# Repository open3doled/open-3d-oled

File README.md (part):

# Open3DOLED 

## Beta Testers Needed
I'm looking for beta testers who have potentially compatible displays.
I have 49 partially assembled units.
If you have a 120hz TV and it is either and OLED with BFI (@120hz), or an LCD with fast pixel response time your display may work, checkout [this fantastic table](https://www.rtings.com/tv/tools/table/138933) provided by rtings.com for relevant display parameters.
Just to be clear the beta units are not free, but produced near cost and bundled with a pair of panasonic glasses with custom firmware optimized for software pageflipping (see below for details about this).
The price for the emitter and 1 pair of M size glasses is $100 USD with tracked global shipping.
I will help you configure the unit to work with your display and help with any trouble shooting, if the unit does not work with your TV you can return it for a refund (minus cost of shipping).
In return all I ask is that you share the config settings that work best with your TV.
If interested contact me at: support at open3doled dot com.

## Introduction
Open3DOLED is a set of software and hardware designs that allow one to turn any display into a 3D display using compatible shutter glasses.  
It works best for displays that incorporate Black Frame Insertion (BFI) technologies and have framerates that exceed 120hz.  
This includes OLED TV's by the likes of LG and Sony which incorporate technologies like LG "Motion Pro" and Sony "Clearness" settings.  
It can also work on LCD TV's and monitors that have fast pixel response time, in such cases it works best if the TV supports HDMI/DVI QFT (Quick Frame Transport), this can be used to force a large vertical blanking interval during which time the image on the LCD will be static.  
It also has been tested to work on the latest Sony micro-LED TV's.  
If your compatibility information for your TV is not listed below, or you are considering buying a TV and would like to know if it might be compatible I would suggest referring to [this fantastic table](https://www.rtings.com/tv/tools/table/138933) provided by rtings.com  
You can compare, sort and filter by pixel response time, support for BFI 120hz, BFI duty cycle, PWM backlight fruency and duty cycle.  
In addition to the RTINGs website you will also need to confirm the orientation of the front polarizer on your TV. 
Most TV's have a vertical front polarizer, but about 10% have a horizontal front polarizer. 
In the event you have have one of these TV's there is a $30 USD extra fee for me to flip the front polarizer on each pair of glasses.
I have measured the front polarization of over 70 different modern TV's and provided them in the FAQ, if your TV isn't listed you can check the front polarization using a pair of polarized sunglasses from the dollar store. 
Polarized sunglasses are vertically polarizer, just like the majority of TVs so if you can see the TV throught the glasses then your TV has a vertical front polarizer (or no polarizer at all).
There is a webstore in the works where you will be able to buy a pre-built/pre-programmed emitter unit in the next month or so once preliminary beta testing is complete..  
In the future custom firmware images that are optimized for software pageflipping for popular brands of glasses by Panasonic (and other manufacturers) may be released.  
(I plan to sell these glasses on the webstore initially along with the emitters to help recoup the over 400(?) hours put into this project, they reduce jitter greatly and eliminate crosstalk from dropped frames)  
Gaming is also supported through the use [Geo3D](https://github.com/open3doled/Geo3D/releases) and [WibbleWobble](https://github.com/PHARTGAMES/WibbleWobbleCore) see below for more details.

## Glasses Warning
* If you are using Panasonic Gen2 (TY-EW3D2XX) glasses, do NOT turn them on while a USB charging cable is attached or you risk destroying the left shutter element from DC bias.
* If you are using Panasonic Gen3 (TY-EW3D3XX) glasses, ONLY use a micro-usb power cable (like the one included), do not use a micro-usb cable with data lines or you risk destroying the right shutter element  from DC bias.
* I didn't design the hardware for these glasses so unfortunately I cannot fix this issue, anything more than 1-2 seconds risks damaging them so always check the shutter elements aren't black when you plug them and unplug it quickly if they are, just incase you are using the wrong cable. (please be careful).

## Getting Started

### Configuring TV or Monitor
* Set your TV to 1080p 120hz (this system should work with 4K 120hz but hasn't been tested yet)
* If your TV switches into ALLM (Auto Low-Latency Mode), disable ALLM as detailed in the FAQ below.
* On LG TV's you need to set OLED Motion Pro to the maximum value.
* On Sony TV's you need to set Motion Flow Clearness setting to MAX
* If you are using a high refresh rate monitor you will benefit from looking into QFT (HDMI quick frame transport) see [instructions](3DPlayer/settings/viewsonic_xg2431/how_to_setup_custom_resolution_with_quick_frame_transport.txt).

### Calibration and Playback
* Linux
  * Install 3DPlayer as described below.
* Windows
  * If you are using a display and glasses for which both an emitter_settings.json and display_settings.json file is available under the settings folder you can skip installing 3DPlayer and use [PotPlayer](PotPlayer/README.md) directly.
  * It is still recommended to install the 3DPlayer if you have time to ensure optimal calibration.
  * If either your glasses or display don't have a settings.json file you will need to install 3DPlayer as described below to perform calibration of the emitter and screen parameters.
  * Once calibration if you intend to use PotPlayer is complete save the required AVI-Synth script by clicking "Generate PotPlayer AVISynth Script" under "Display Settings", then load this script into PotPlayer.

## 3DPlayer Installation Instructions:

### Ubuntu Install:
* First time installation
```
apt update
apt upgrade
apt install git git-gui
cd ~
git clone https://github.com/open3doled/open-3d-oled.git
cd open-3d-oled/3DPlayer
sudo apt install gobject-introspection gstreamer1.0-tools gstreamer1.0-plugins-base gstreamer1.0-gtk3 gstreamer1.0-plugins-bad libgstreamer-plugins-bad1.0-0 gstreamer1.0-plugins-good gstreamer1.0-plugins-ugly python3-gst-1.0 gstreamer1.0-libav
sudo apt install python3 python3-pip python3-virtualenv python3-virtualenvwrapper python3-tk python3-pil.imagetk idle3 gstreamer1.0-python3-plugin-loader
sudo apt install python3-gi
echo "export WORKON_HOME=$HOME/.virtualenvs" >> ~/.bashrc
echo "VIRTUALENVWRAPPER_PYTHON=/usr/bin/python3" >> ~/.bashrc
echo "source /usr/share/virtualenvwrapper/virtualenvwrapper.sh" >> ~/.bashrc
mkvirtualenv --system-site-packages open3doled
pip install -r requirements.txt
  if pyopengl-accelerate fails to install due to some numpy error https://github.com/mcfletch/pyopengl/issues/118 and your system has numpy installed via apt already you can try either of the following.
  ignore the system numpy with: pip install --ignore-installed -r requirements.txt
  don't use pyopengl-accelerate: remove pyopengl-accelerate from requirements.txt
python3 3d_player.py
```
* Running subsequently
```
workon open3doled
python3 3d_player.py

OR

~/.virtualenvs/open3doled/bin/python3 3d_player.py
```

### Windows Release Install:
* Download the latest release version from the [Releases page](https://github.com/open3doled/open-3d-oled/releases) under Assets.
* Unzip and run 3d_player.exe
* The first time you run the program it can take a while to load all required libraries, please be patient.

If running windows 11 or 10 with DPI scaling be sure to disable it as follows.
1) Right click properties on 3d_player.exe in the 3DPlayer folder
2) Click on "Compatability" tab then click on the button at the bottom "Change high DPI settings"
3) At the very bottom check the box next to the text "Override high DPI scaling behavior. Scaling performed: Application"
4) Click OK on this sub dialog as well as the parent one

### Calibration

* Put the sensor bar on the top left corner of your TV and connect it to the PC you will be using to play your 3D videos.
* Start Open3DOLED 3DPlayer
* Click the "Open emitter settings" icon button on the main toolbar, and then in the emitter settings window "Connect" to your 3d emitter
* Click on "Load Settings From Disk" and select a profile for your TV and glasses from the "settings" directory. Some settings files are optimized to reduce vignetting (black at top and bottom of screen) and others are optimized to reduce ghosting (cross talk between left and right eye at top and bottom of screen), choose the settings file matching your preference.
* If you are using a none OLED display or a display for which settings are not already available it is recommended that you set "OPT101 Ignore All Duplicates" to 1. This can be disabled later, but will ensure the highest possibility the emitter can synchronize to your TV.
* If necessary change the "IR Protocol" to match your glasses, most settings templates should have this set correctly already. (Optional)
* Click "Update Settings" to send these settings to the emitter (Leave this window open but you can let it go into the background)
* Click the "Open disply settings" icon button on the main toolbar, and then the checkbox that says "Calibration Mode" at the bottom you can close this window.
* Click the "Open a video file for playback" icon button on the main toolbar, then click the "Select" button next to "Video File" and from the videos directory choose the file "ghosting_test_video_1080p_red_left_blue_right_side_by_side_full.mp4" then click "Open"
* Use F11 or the "Toggle fullscreen" icon button on the main toolbar to make the video fullscreen if it does not automatically go fullscreen
* Perform calibration using the onscreen callibration instructions paying consideration to the following points
  * Position the emitter and trigger boxes.
  * Adjust timing with a goal of either optimizing for zero ghosting (with some minor vignetting at top and bottom) or vignetting (with some minor ghosting at top and bottom).
* When you are happy with the calibration settings you can press the escape key to close the video or F11 to minimize the playback window.
* Next navigate back to the emitter settings window, you should see that "Frame Delay" and "Frame Duration" have no been updated to the optimized values obtained during calibration.
* Click "Save Settings to EEPROM" to make these settings persist next time your power up the 3d emitter.
* Click "Save Settings to Disk" to make a copy of your optimized 3d emitter settings locally incase for whatever reason you decide to experiment with a different type of 3d glasses.
* Click the "Open disply settings" icon button on the main toolbar, and disable the checkbox that says "Calibration Mode", you should see that the "Whitebox Vertical Position" has changed from "0" to whatever value you aligned it with.
* Click "Save Settings to Disk" to make a copy of your optimized display settings locally incase for whatever reason you decide to experiment with a different display.
* Click "Close" on the display settings window.
* Your now done and should be able to watch 3D videos on your OLED!
* Refer to this video for an example using a slightly dated version of the software if you need a demonstration of this proceedure https://youtu.be/tEjXUV8hVDs
    
### Command Line Interface
3DPlayer supports a simple command line interface for integration into systems like Kodi, if you implement scripts for a video management s ystem please let us know so we can link to them here.
If the "video-path" command line argument is supplied it will auto launch playback of that video using the default settings you have stored from prior usage.
Defaults can be overriden using additionally avaiable command line arguments to support videos with different formats and subtitle files.
```
Linux (in terminal):
python3 3d_player.py --video-path ./videos/ghosting_test_video_1080p_red_left_blue_right_side_by_side_full.mp4 --frame-packing side-by-side-full --right-eye right --display-resolution 1920x1080
Windows (in command prompt):
3d_player.exe --video-path ./videos/ghosting_test_video_1080p_red_left_blue_right_side_by_side_full.mp4 --frame-packing side-by-side-full --right-eye right --display-resolution 1920x1080
3d_player.exe --video-path "C:\open-3d-oled\3DPlayer\videos\ghosting_test_video_1080p_red_left_blue_right_side_by_side_full.mp4" --frame-packing side-by-side-full --right-eye right --display-resolution 1920x1080
```

## PotPlayer
For those who want the best and most versatile playback performnce on Windows it is recommended to use [PotPlayer](PotPlayer/README.md). 
Click [here](PotPlayer/README.md) for instructions on how to setup and PotPlayer.

## MPC Video Renderer (Experimental)
There is also an experimental Open3DOLED fork of MPC Video Renderer with integrated software pageflipping and emitter integration.
* [MPCVideoRenderer/Readme.md](MPCVideoRenderer/Readme.md)
* Even though this path is still experimental, it is currently the preferred method on Windows due to better performance, built-in calibration, and integration of the most important features from the Python-based 3DPlayer.
* Keep your existing player/renderer setup available as a fallback while testing.

## Gaming
* If you have a fast PC that can maintain 120hz and you want to play traditional 2D games that are DX 11 or DX 12 you can try out a modified version of [Geo3D](https://github.com/open3doled/Geo3D/releases) to support the Open3DOLED trigger boxes. Game support is somewhat limited but it does work well for certain games.
* If you are planning to play traditional games and use reshades SuperDepth3D or any SteamVR games then check out [WibbleWobble](https://github.com/PHARTGAMES/WibbleWobbleCore) the author kindly added  support for the Open3DOLED trigger boxes.
  * WibbleWobble launches a separate process that performs 120hz page flipping reliably even when your CPU is under heavy load so that you will get minimal dropped frames.
  * Additionally WibbleWobble has a custom module to communicate over usb information about which eye is showing. If anyone wants it I can build a custom version of the firmware that accepts these messages to trigger the shutter glasses directly, eliminating the need to put the unit on your TV or monitor when using WibbleWobble for gaming. Just let me know if you want this.
    
## FAQ, Useful Commands and Tips
* The sensor bar once configured does not need to be connected to your PC unless you are using advanced debugging features. It can be connected to the USB power on the back of your TV.
* Supported TVs
```
Working (Tested)
 - LG C1 OLED (Fully working with Motion Pro high setting with no crosstalk due to ~41% BFI duty cycle)
   - C1 55 and 83 inch both seem to have a vertical front polarizer which works well with panasonic glasses.
   - C1 65 appears to have a horizontal front polarizer (at least on one beta testers unit), requiring for the pansonic glasses that you to either flip the LCD elements or hold the glasses backward.
 - Sony OLED XBR 48a9s (Working with clearness high setting but the bottom and top 10% of the screen has crosstalk due to ~61% BFI duty cycle)
 - Viewsonic XG2431 (Works perfectly zero-ghosting without any BFI enabled at up to 144 hz shutter glasses refresh speed, you online need to setup a custom quick frame transport HDMI profile to get a blanking interval that matches more than 40% of the screen duty cycle, see https://forums.blurbusters.com/viewtopic.php?t=8946 or read the document in the corresponding settings folder)
 - Asus VG248QE LightBoost Capable (Works perfectly with [LightBoost enabled](https://blurbusters.com/zero-motion-blur/lightboost/), Works usably with lightboost turned off using "OPT101 Ignore All Duplicates")
Partially Working (Tested)
 - Sony X95K MiniLED (Used with "OPT101 Ignore All Duplicates", "Block Signal Detection Delay" 7500, on tv disable "Local Dimming" to reduce ghosting at top of screen, BFI 1, and run at native 1080p from pc)
Untested (But should work well)
 - LG CX/GX/G1 OLED (These should work identical to LG C1 OLED but are as of yet untested)
 - Other OLEDs with 120hz BFI technology.
 - Any monitor without BFI with at least 144hz at 1080p and a G2G (grey to grey) pixel refresh under 1ms (Used with "OPT101 Ignore All Duplicates") (You will need to setup an HDMI QFT quick frame transport monitor profile and run the glasses at 110 or 120 hz)
Untested (But should work ok)
 - Any monitor without BFI with at least 120hz at 1080p and a G2G (grey to grey) pixel refresh under 1ms (Used with "OPT101 Ignore All Duplicates") (You will need to setup an HDMI QFT quick frame transport monitor profile and run the glasses at 90 or 100 hz)
Not Working (Untested)
 - LG C2/G2 OLED (Missing 120hz BFI)
 - LG C3/G3 OLED (Missing 120hz BFI)
```
* TV Polarization Warning (PLEASE READ)
```
About 90% of TV's I tested at the store are polarized with a vertical front polarizer however 10% (most commonly those with 65 inch displays) have horizontal polarization.
In the event your TV has a horizontal front polarizer you will need to flip the lens elements and reverse left and right on the panasonic glasses to use them with your TV.
Alternatively you can hold the glasses, upside down and backwards to watch the movie but this isn't really viable long term.
Flipping the lens elements is difficult but doable (easier on the gen3 glasses but still difficult) with some practice, expect to break at least afew pairs if it is your first time solder flexible PCB's.
Also be sure to cover up the lens element with some tissue to avoid solder from flying onto the glasses lens when the ribbon cable unsolders as it is "spring loaded".
I can provide glasses with flipped lens elements for an additional $20 per pair as resoldering them takes about 40 mins per pair and the probability of breaking or damaging a pair in the process is high.

Computer monitors are a bit more mixed some older and even some newer monitors have +/- 45 degree polarization.
With +/- 45 degree polarization I believe your best option for brightness is to use nvidia 3d vision glasses, as glasses with either horizontal or vertical front polarizing film will lose half their brightness.
You can verify if your monitor has 45 degree polarization as if you rotate sunglasses to +45 or -45 one of them should make the screen go dark.

The Panasonic (and sony if I remember right) glasses natively require a non-horizontal (perferably vertical) polarizer on the front of the TV to work without flipping the lens.
It seems to be very variable even from the same manufacturer and same model for example LG C1 55 has vertical but LG C1 65 has horizontal.
My best current guess is that the polarizer film they use the coat the front of the TV's comes on a roll with a width that is slightly too small to fit two 65 inch screens side by side so tehy rotate it vertically to maximize film utilization.
If you are unsure about your TV please check using a pair of polaroid sunglasses before purchasing any glasses from me. Cheap polaroid sungless can normally be found at the dollar store for $2 or there abouts.
Polaroid sungless have a vertical front polarizer just the same as the Panasonic glasses in their default configuration.

I went to my local electronics store and recorded the polarization of various TV's front polarizers they are listed below, but please double check your TV just to be sure!

HISENSE
  43A6K             v
  50A6K             v
  65U7H             v
  65U8N             v
  65UX              v
  
LG
  OLED42C3PJA       v
  OLED48B4PJA       v
  OLED55B2PJA       v
  OLED65B2PJA       h
  OLED65B3PJA       h
  
ORION
  OSW40G10          v
  
PANASONIC
  TH-43LF1          v
  TH-50MR770        v
  TH-55LW1          v
  TH-55MZ1800       v
  TH-65MX950        v
  TH-75MX950        v
  TV-42Z85A         v
  TV-43W80A         v
  TV-43W90A         v
  TV-48Z85A         v
  TV-50W90A         v
  TV-55W90A         v
  TV-55Z90A         v
  TV-55Z95A         v
  TV-65W90A         v
  
SHARP
  2T-C42BE1         v
  4T-C43FN2         v
  4T-C43GP2         v
  4T-C50FN2         v
  4T-C50GP2         v
  4T-C55FN2         v
  4T-C55EP1         v
  4T-C55GN1         v
  4T-C55GP1         v
  4T-C55GS1         none
  4T-C55GN2         v
  4T-C65FL1         v
  4T-C65FS1         none
  4T-C65GN1         v
  4T-C65GP1         v
  4T-C65GQ1         h
  4T-C65GS1         none
  4T-C75EL1         v
  4T-C75GN1         v
  8T-C65DX1         h
  8T-C75DX1         v
  
SONY
  KJ-43X80L         v
  KJ-43X85K         v
  KJ-50Z80L         v
  KJ-50X85K         v
  K-55XR70          v
  K-55XR80          v
  XRJ-48A90K        v (maybe none not sure)
  XRJ-50X95K        v
  XRJ-55A80L        v
  XRJ-55X90L        v
  XRJ-65A95K        none
  XRJ-65X90L        v
  XRJ-65X95L        h (not entirely sure about this one)
  XRJ-75X90L        v
  
TCL
  40S5400           v
  40S54H            v
  43C645            v
  43P63H            v
  55C645            v
  55P655            v
  
TOSHIBA
  REGZA 40V35N      v
  REGZA 43Z570L     v
  REGZA 48X8900N    v
  REGZA 50M550M     v
  REGZA 50Z570L     v
  REGZA 55M550M     h
  REGZA 55Z670N     v
  REGZA 55Z870N     v
  REGZA 55Z870M     v
  REGZA 55X9900N    v
  REGZA 55X8900N    v
  REGZA 65Z670N     v
  REGZA 65Z870N     v
  REGZA 65Z970N     v
  REGZA 65X9900N    h
  REGZA 65X8900N    h
  REGZA 75Z970N     v

XIAOMI
  R23Z012A          v
  R23Z013A          v

```
* If you are using a non OLED display or a display for which settings are not already available it is recommended that you set "OPT101 Ignore All Duplicates" to 1 under Emitter Settings. This will ensure the highest possibility the emitter can synchronize to your TV, at the cost of not being able to detect duplicate frames and inform the glasses to resynchornize immediately. It will typically result in a resynchronization delay of 1-2 frames on a duplicate frame, you may be able to get satisfactory results without using this by tuning "OPT101 Block Signal Detection Delay" and "OPT101 Block N Subsequent Duplicates" to match your display characteristics.
* If you are using an LCD you will want to use HDMI QFT "Quick Frame Transport" (if available) to force a long blanking interval between frames. You basically run the monitor clock at for example 240hz but only send 120hz of data. That way 50% of the time the monitor will not be updating the physical screen. During this time the shutter glasses will open and show an image with minimal ghosting. Take a look at these [instructions](3DPlayer/settings/viewsonic_xg2431/how_to_setup_custom_resolution_with_quick_frame_transport.txt) for more details of how to enable this.
```
* If you display supports BFI and it is an LCD make sure the BFI is phase synchronized to the actual refresh rate. I do not believe this is actually done on many monitors. Even Viewsonic XG2431 doesn't phase synchronize it and you need to do this manually using the blurbusters tool. Unless the BFI/strobing is phase synchronized you may be better to just turn it off.
* Performance is best on Linux (tested on Ubuntu 20.04 an 22.04) followed by Windows 10 then Windows 11. I haven't tested on Windows 7.
* On Windows 11 when using a 4k display sometimes Windows decides to use "Active Signal Mode" resolution of 4k and have a "Display Resolution" of 1080p. This confuses the software so make sure your "Active signal mode" and "Display Resolution" match at either 1080P or 4K. Most users will not want to change this as it will cause text to be tiny on your PC but there is a workaround where this setting can be applied only to the 3d_player software, the following steps detail that process.
1) right click on the 3d_player.exe and goto "Properties"
2) select the compatabillity tab from the top
3) down near the bottom click the button "Change high DPI settings"
4) a new window titled "High DPI settings for 3d_player.exe" should open.
5) at the bottom select the checkbox next to "Override high DPI scaling behavior. Scaling performed by:"
6) click OK to close the window "High DPI settings for 3d_player.exe"
7) click OK to close the window "3d_player.exe Properties"
8) Now when you use the program on a screen with High DPI scaling the software should function with all necessary elements at the correct size.
```
* HDMI bitstream audio passthrough may have issues on some computers, if you are having difficulty it is recommended to disable HDMI audio passthrough and confirm the audio works on your local PC.
* For test videos beyond the calibration videos below are some recommendations (note the mvc mkv files will only work under PotPlayer currently).
```
   https://web.archive.org/web/20250128062429/http://bbb3d.renderfarming.net/download.html
   https://kodi.wiki/view/Samples#3D_Test_Clips
```
* If gstreamer cannot initiate playback on a playback pipeline it will timeout after 15 seconds.
* GStreamer has difficulty processing matroska packed videos with multi-language audio streams that have 5.1 or 7.1 channel audio, removing all but the language you want from the file can solve playback issues. This can be performed with ffmpeg as follows.
```
   ffmpeg -i Movie.7xAudio.mkv -map 0:v:0 -map 0:a:0 -c copy Movie.7xAudio.EngOnly.mkv
```   

* **Display switches into ALLM / Game Mode:** Some TVs disable the BFI required by Open3DOLED when ALLM is active. The preferred, GPU-independent fix is to open [ToastyX CRU](https://www.monitortests.com/forum/Thread-Custom-Resolution-Utility-CRU), select the affected display, edit `CTA-861 Extension Block` -> `HDMI 2.1 support`, disable `Auto low-latency mode`, save, then run `restart64.exe` or reboot. This removes ALLM support from the display capabilities presented to the GPU. As an AMD-only fallback, verify the correct GPU entry under `HKLM\System\CurrentControlSet\Control\Class\{4d36e968-e325-11ce-bfc1-08002be10318}\0000` (or `0001`, `0002`, etc.), set the `DalHdmiEnableALLM` DWORD to `0` (`1` enables it), and reboot. If CRU has no relevant CTA-861/HDMI 2.1 block, disabling exclusive fullscreen in PotPlayer may avoid triggering ALLM, but does not disable ALLM itself.
* **AMD display switches from 120 Hz to 60 Hz in fullscreen:** This is a separate mode-selection problem, not an ALLM problem. In CRU, select the affected display and remove `1920x1080 @ 50 Hz`, `1920x1080 @ 60 Hz`, the `1920x1080 @ 60 Hz` Standard Resolution, and the 50/60 Hz entries under `CTA-861 Extension Block` -> `TV resolutions`; then run `restart64.exe` or reboot. This workaround removes those modes from Windows and should only be used on affected systems. `reset-all.exe` clears all CRU overrides and is not used to apply changes.

* Emitter not working
```
   Sometimes when changing the glasses IR Protocol the emitter will enter an unresponsive state. If this happens save your settings to EEPROM and disconnect and reconnect it's power.
```
* If during development you get the error "Unable to find/initialize GStreamer plugin GSTPageflipGLSink." it can sometimes be solved by removing the gstreamer registry cache (and/or rebooting).
```
   rm  ~/.cache/gstreamer-1.0/registry.x86_64.bin
   rm "C:\Users\[USERNAME]\AppData\Local\Microsoft\Windows\INetCache\gstreamer-1.0\registry.x86_64-mingw.bin"
```  
* If you need to use line profiling to do performance analysis of gstpageflipglsink.py then use the following modified version of line profiler with a global enable flag and max time tracking.
```
   pip install git+https://github.com/46cv8/line_profiler.git@max_time ps
``` 
* On Linux based operating systems if you experience dropped/duplicate frames every few seconds you may benefit form disabling compositing if possible. Many window managers will auto bypass compositing with ["fullscreen unredirect"](https://www.reddit.com/r/linux_gaming/comments/u6dckj/comment/i57o5r4/) when you swtich to fullscreen mode, not to be confused with fullscreen windowed mode.

## Development Installation Instructions

### Windows Developer Install:
```
  - install msys2 (https://stackoverflow.com/questions/37460073/msys-vs-mingw-internal-environment-variables)
  - follow steps at https://pygobject.readthedocs.io/en/latest/getting_started.html
  - open ucrt64 shell
  - pacman -S git
  - git clone https://github.com/open3doled/open-3d-oled.git 
  - due to potential issues with the latest msys2 packages not working a copy of the latest working pacman database files are provided it is recommended you copy them over if you are having difficulty getting a build to work
    - cp -rf open-3d-oled/3DPlayer/building/msys2_pacman_db_files/* /var/lib/pacman/sync
  - pacman -Su (you can use "pacman -Suy" here to update your database files if you are trying to build using the latest packages otherwise omit the y option) (you will need to restart your ucrt64 shell after this)
  - pacman -Su
  - pacman -S mingw-w64-ucrt-x86_64-gtk4 mingw-w64-ucrt-x86_64-python3 mingw-w64-ucrt-x86_64-python3-pip mingw-w64-ucrt-x86_64-python3-gobject mingw-w64-ucrt-x86_64-python-pygame mingw-w64-ucrt-x86_64-python-pyopengl mingw-w64-ucrt-x86_64-python-pyopengl-accelerate mingw-w64-ucrt-x86_64-python-numpy mingw-w64-ucrt-x86_64-python-cffi mingw-w64-ucrt-x86_64-python-wheel mingw-w64-ucrt-x86_64-python-pillow mingw-w64-ucrt-x86_64-python-pyusb mingw-w64-ucrt-x86_64-python-pyserial 
  - pacman -S mingw-w64-ucrt-x86_64-gstreamer mingw-w64-ucrt-x86_64-gst-devtools mingw-w64-ucrt-x86_64-gst-plugins-base mingw-w64-ucrt-x86_64-gst-plugin-gtk mingw-w64-ucrt-x86_64-gst-plugins-bad mingw-w64-ucrt-x86_64-gst-plugins-bad-libs mingw-w64-ucrt-x86_64-gst-plugins-good mingw-w64-ucrt-x86_64-gst-plugins-ugly mingw-w64-ucrt-x86_64-gst-python mingw-w64-ucrt-x86_64-gst-libav
  - pacman -S mingw-w64-ucrt-x86_64-python-psutil
  - pip install pysrt cairosvg pyinstaller pysdl2
  - building libgstpython.dll (https://gstreamer.freedesktop.org/documentation/installing/building-from-source-using-meson.html?gi-language=python)
    - pacman -S git mingw-w64-ucrt-x86_64-meson-python mingw-w64-ucrt-x86_64-cc mingw-w64-ucrt-x86_64-meson mingw-w64-ucrt-x86_64-ninja mingw-w64-ucrt-x86_64-pkg-config mingw-w64-ucrt-x86_64-pygobject-devel mingw-w64-ucrt-x86_64-python
    - git clone https://gitlab.freedesktop.org/gstreamer/gstreamer.git
    - cd gstreamer
    - git checkout 1.22.9
    - cd subprojects/gst-python/
    - meson build
    - cd build
    - ninja
    - cp plugin/libgstpython.dll /ucrt64/lib/gstreamer-1.0/libgstpython.dll
  - cd open-3d-oled/3DPlayer
  - fix to ensure gst-plugin-scanner.exe builds a valid gstreamer plugin cache including our python plugin.
    - export PYTHONLEGACYWINDOWSDLLLOADING=1
  - test the application
    - python3 3d_player.py

  - if you run into issues where it says "Unable to find/initialize GStreamer plugin GSTPageflipGLSink." try deleting the gstreamer plugin registry
    - rm "C:\Users\[USERNAME]\AppData\Local\Microsoft\Windows\INetCache\gstreamer-1.0\registry.x86_64-mingw.bin"
 
  - If you run into issues about "ImportError('DLL load failed while importing _gi: The specified module could not be found.'))" try either of the following
    - export PYTHONLEGACYWINDOWSDLLLOADING=1
    - mv /ucrt64/libexec/gstreamer-1.0/gst-plugin-scanner.exe /ucrt64/libexec/gstreamer-1.0/gst-plugin-scanner.exe.bak
   
  - If the application fails with an error about Gst bad types make sure you don't have reminants from a pyinstaller build still around
    - rm -rf ~/open-3d-oled/3DPlayer/build
    - rm -rf ~/open-3d-oled/3DPlayer/dist
```
  
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
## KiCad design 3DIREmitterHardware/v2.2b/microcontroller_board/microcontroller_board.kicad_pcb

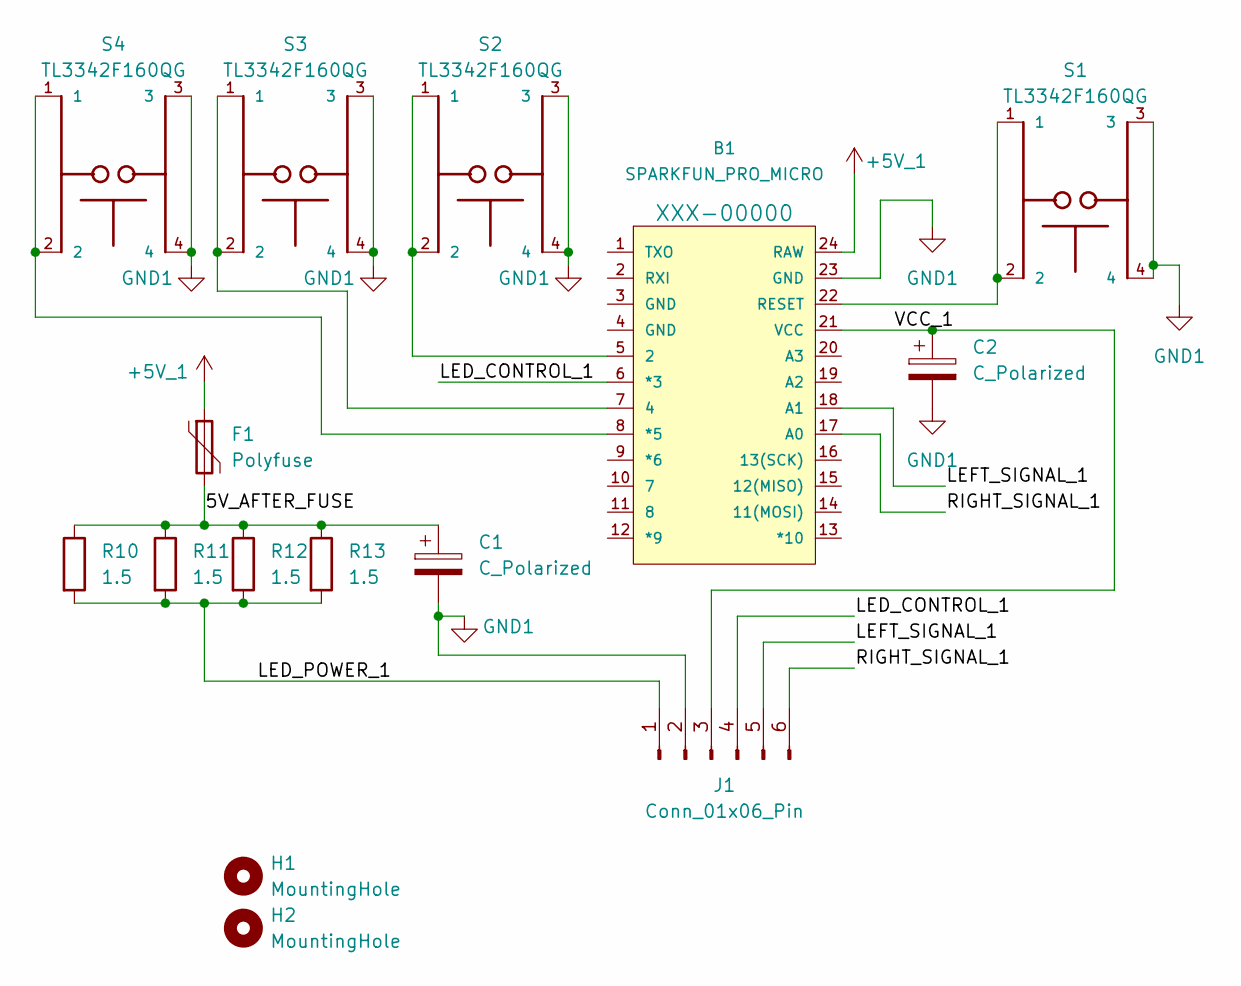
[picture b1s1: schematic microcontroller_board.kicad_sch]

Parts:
B1: SPARKFUN_PRO_MICRO
C1, C2: C_Polarized; C_Radial_D6.3mm_H11.0mm_P2.50mm
F1: Polyfuse; Fuse_0805_2012Metric_Pad1.15x1.40mm_HandSolder
H1, H2: MountingHole; MountingHole_1.6mm_M1.4_ISO7380
J1: Conn_01x06_Pin; PinHeader_1x06_P2.54mm_Vertical
R10, R11, R12, R13: 1.5; R_2512_6332Metric_Pad1.40x3.35mm_HandSolder
S1, S2, S3, S4: TL3342F160QG; SW_TL3342F160QG

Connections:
+5V_1: B1.24 (RAW), F1.1
/5V_AFTER_FUSE: C1.1, F1.2, R10.1, R11.1, R12.1, R13.1
/LED_CONTROL_1: B1.6 (*3), J1.4
/LED_POWER_1: J1.1, R10.2, R11.2, R12.2, R13.2
/LEFT_SIGNAL_1: B1.18 (A1), J1.5
/RIGHT_SIGNAL_1: B1.17 (A0), J1.6
/VCC_1: B1.21 (VCC), C2.1, J1.3
GND1: B1.23 (GND), C1.2, C2.2, J1.2, S1.3, S1.4, S2.3, S2.4, S3.3, S3.4, S4.3, S4.4
unnamed: B1.5 (2), S2.1, S2.2
unnamed: B1.7 (4), S3.1, S3.2
unnamed: B1.8 (*5), S4.1, S4.2
unnamed: B1.22 (RESET), S1.1, S1.2

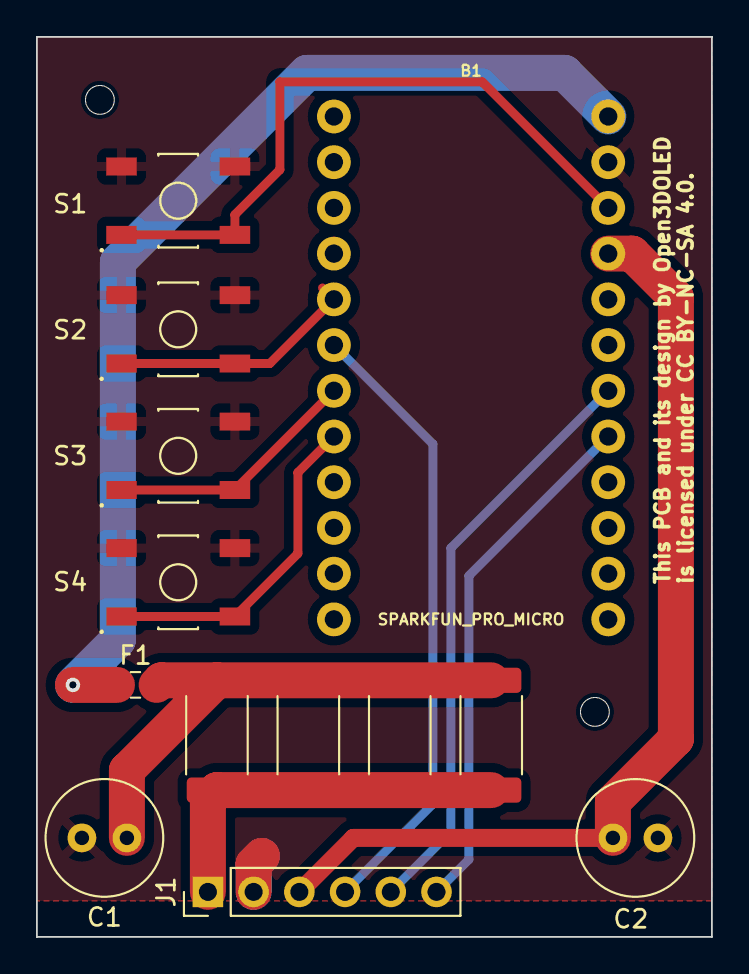
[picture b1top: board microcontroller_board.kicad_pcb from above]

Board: 2 copper layers, 37.5 x 50.0 mm, 15 parts (0 on the bottom side), 12 nets.

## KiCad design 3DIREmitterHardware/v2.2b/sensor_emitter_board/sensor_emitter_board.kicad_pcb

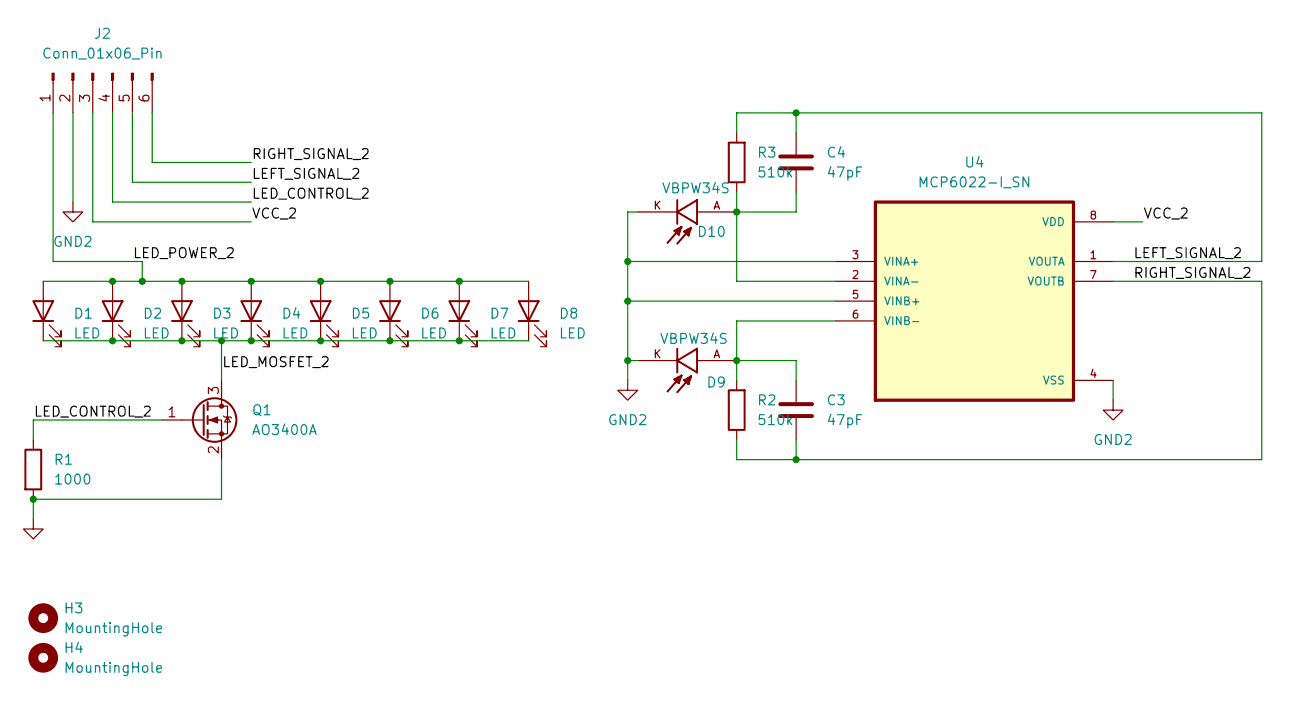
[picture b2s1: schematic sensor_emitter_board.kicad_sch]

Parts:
C3, C4: 47pF; C_0603_1608Metric_Pad1.08x0.95mm_HandSolder
D1, D2, D3, D4, D5, D6, D7, D8: LED; LED_1210_3225Metric_Pad1.42x2.65mm_HandSolder
D9, D10: VBPW34S; XDCR_VBPW34S; PARTREV 1.2; DigiKey_Part_Number 751-1500-2-ND
H3, H4: MountingHole; MountingHole_1.6mm_M1.4_ISO7380
J2: Conn_01x06_Pin; PinHeader_1x06_P2.54mm_Vertical
Q1: AO3400A; SOT-23
R1: 1000; R_0603_1608Metric_Pad0.98x0.95mm_HandSolder
R2, R3: 510k; R_0603_1608Metric_Pad0.98x0.95mm_HandSolder
U4: MCP6022-I_SN; SOIC127P599X175-8N

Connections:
/LED_CONTROL_2: J2.4, Q1.1 (G), R1.1
/LED_MOSFET_2: D1.1 (K), D2.1 (K), D3.1 (K), D4.1 (K), D5.1 (K), D6.1 (K), D7.1 (K), D8.1 (K), Q1.3 (D)
/LED_POWER_2: D1.2 (A), D2.2 (A), D3.2 (A), D4.2 (A), D5.2 (A), D6.2 (A), D7.2 (A), D8.2 (A), J2.1
/LEFT_SIGNAL_2: C4.1, J2.5, R3.2, U4.1 (VOUTA)
/RIGHT_SIGNAL_2: C3.2, J2.6, R2.1, U4.7 (VOUTB)
/VCC_2: J2.3, U4.8 (VDD)
GND2: D9.K, D10.K, J2.2, Q1.2 (S), R1.2, U4.3 (VINA+), U4.4 (VSS), U4.5 (VINB+)
unnamed: C4.2, D10.A, R3.1, U4.2 (VINA-)
unnamed: C3.1, D9.A, R2.2, U4.6 (VINB-)

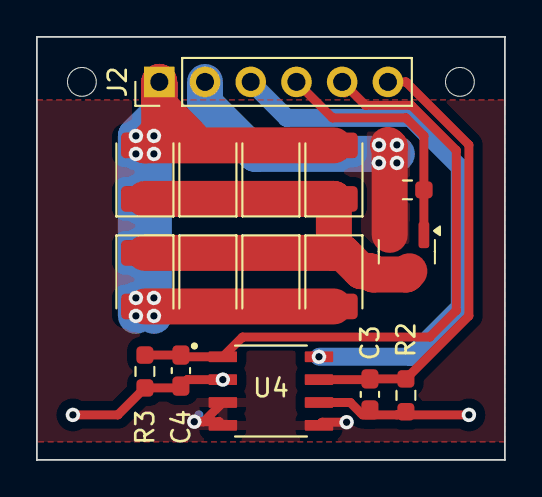
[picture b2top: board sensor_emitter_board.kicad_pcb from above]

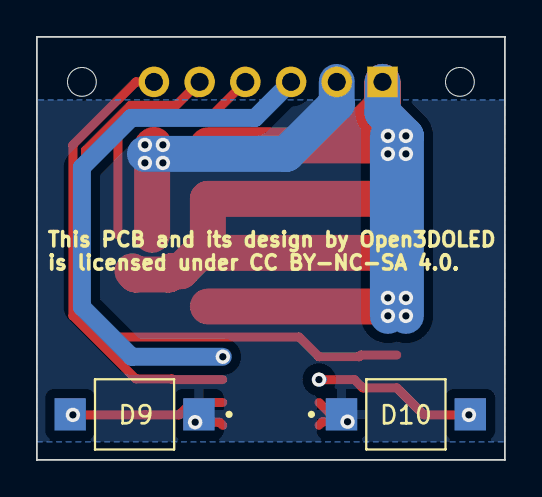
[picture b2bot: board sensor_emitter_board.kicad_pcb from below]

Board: 2 copper layers, 26.0 x 23.5 mm, 20 parts (2 on the bottom side), 9 nets.

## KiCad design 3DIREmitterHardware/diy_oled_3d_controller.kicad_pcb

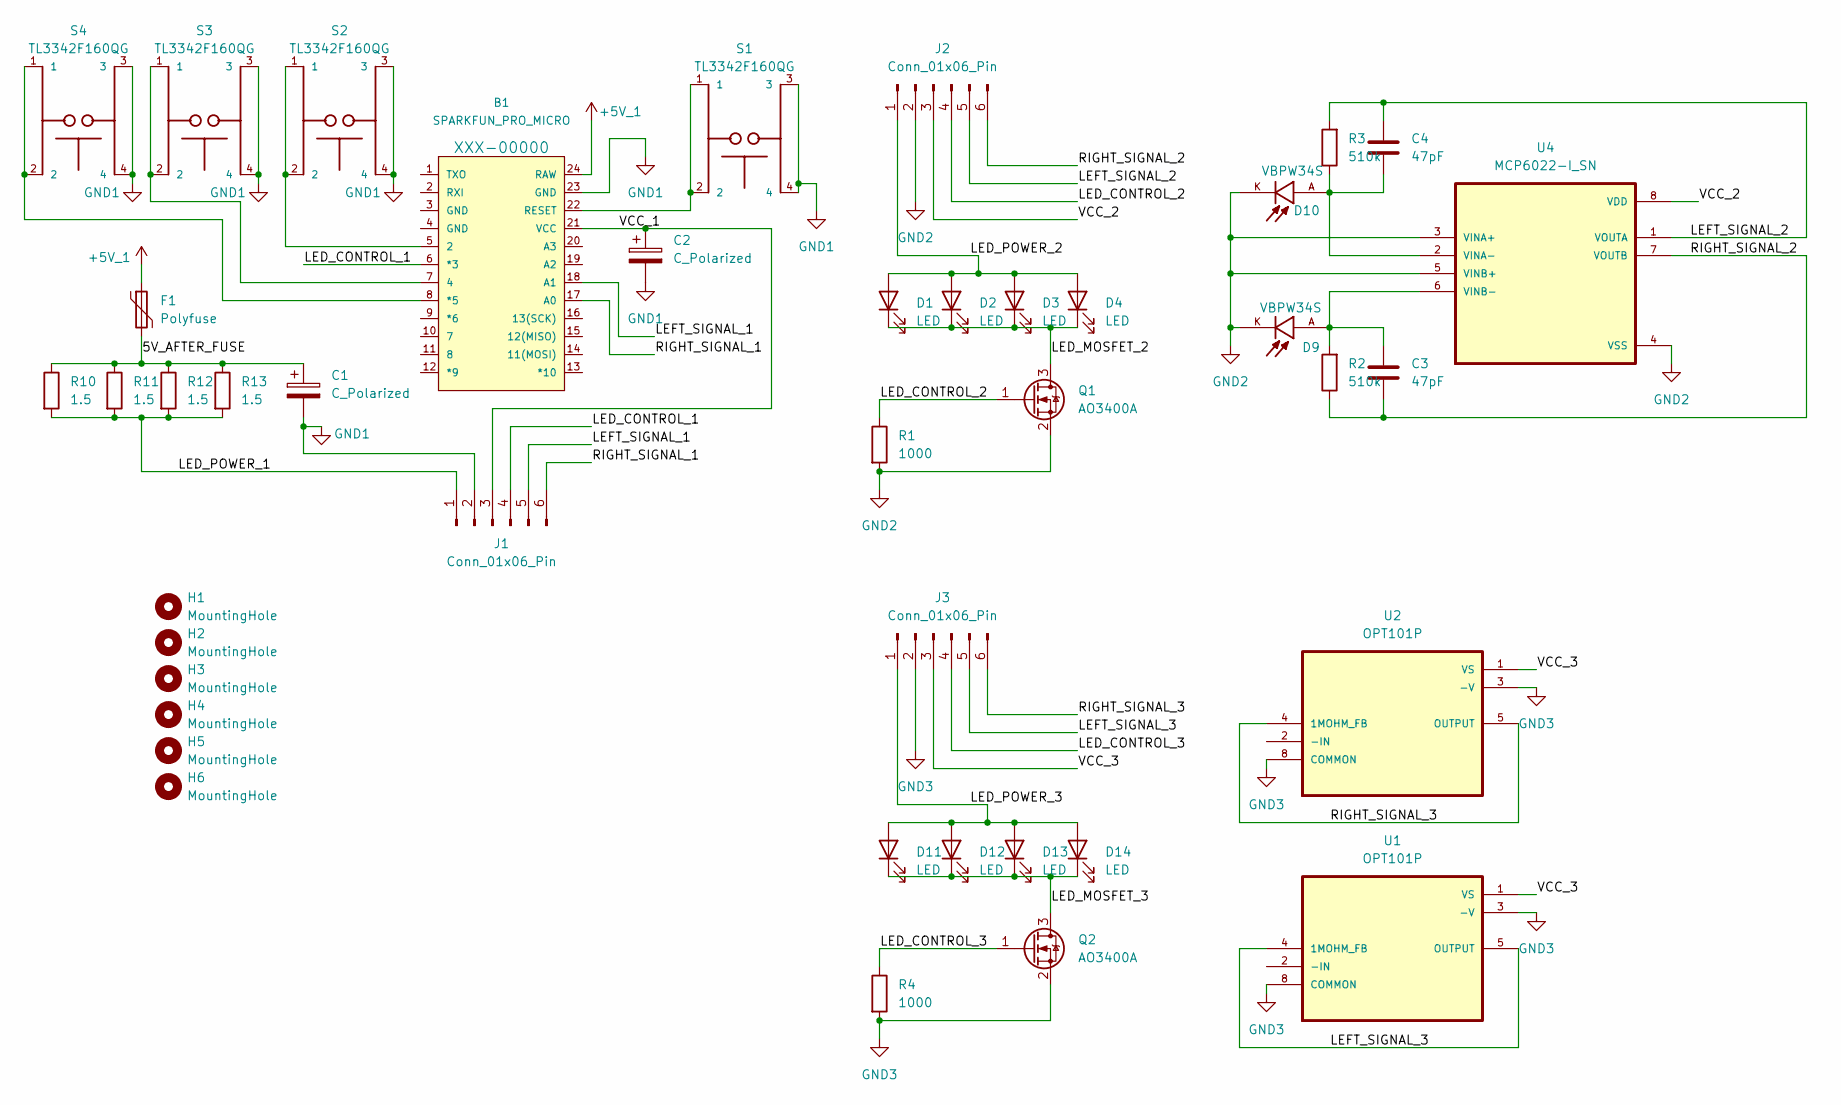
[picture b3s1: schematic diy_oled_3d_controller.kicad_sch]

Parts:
B1: SPARKFUN_PRO_MICRO
C1, C2: C_Polarized; C_Radial_D6.3mm_H11.0mm_P2.50mm
C3, C4: 47pF; C_0603_1608Metric_Pad1.08x0.95mm_HandSolder
D1, D2, D3, D4, D11, D12, D13, D14: LED; LED_1210_3225Metric_Pad1.42x2.65mm_HandSolder
D9, D10: VBPW34S; XDCR_VBPW34S; PARTREV 1.2; DigiKey_Part_Number 751-1500-2-ND
F1: Polyfuse; Fuse_0805_2012Metric_Pad1.15x1.40mm_HandSolder
H1, H2, H3, H4, H5, H6: MountingHole; MountingHole_1.6mm_M1.4_ISO7380
J1, J2, J3: Conn_01x06_Pin; PinHeader_1x06_P2.54mm_Vertical
Q1, Q2: AO3400A; SOT-23
R1, R4: 1000; R_0603_1608Metric_Pad0.98x0.95mm_HandSolder
R2, R3: 510k; R_0603_1608Metric_Pad0.98x0.95mm_HandSolder
R10, R11, R12, R13: 1.5; R_2512_6332Metric_Pad1.40x3.35mm_HandSolder
S1, S2, S3, S4: TL3342F160QG; SW_TL3342F160QG
U1, U2: OPT101P; DIP762W46P254L952H419Q8
U4: MCP6022-I_SN; SOIC127P599X175-8N

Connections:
+5V_1: B1.24 (RAW), F1.1
/5V_AFTER_FUSE: C1.1, F1.2, R10.1, R11.1, R12.1, R13.1
/LED_CONTROL_1: B1.6 (*3), J1.4
/LED_CONTROL_2: J2.4, Q1.1 (G), R1.1
/LED_CONTROL_3: J3.4, Q2.1 (G), R4.1
/LED_MOSFET_2: D1.1 (K), D2.1 (K), D3.1 (K), D4.1 (K), Q1.3 (D)
/LED_MOSFET_3: D11.1 (K), D12.1 (K), D13.1 (K), D14.1 (K), Q2.3 (D)
/LED_POWER_1: J1.1, R10.2, R11.2, R12.2, R13.2
/LED_POWER_2: D1.2 (A), D2.2 (A), D3.2 (A), D4.2 (A), J2.1
/LED_POWER_3: D11.2 (A), D12.2 (A), D13.2 (A), D14.2 (A), J3.1
/LEFT_SIGNAL_1: B1.18 (A1), J1.5
/LEFT_SIGNAL_2: C4.1, J2.5, R3.2, U4.1 (VOUTA)
/LEFT_SIGNAL_3: J3.5, U1.4 (1MOHM_FB), U1.5 (OUTPUT)
/RIGHT_SIGNAL_1: B1.17 (A0), J1.6
/RIGHT_SIGNAL_2: C3.2, J2.6, R2.1, U4.7 (VOUTB)
/RIGHT_SIGNAL_3: J3.6, U2.4 (1MOHM_FB), U2.5 (OUTPUT)
/VCC_1: B1.21 (VCC), C2.1, J1.3
/VCC_2: J2.3, U4.8 (VDD)
/VCC_3: J3.3, U1.1 (VS), U2.1 (VS)
GND1: B1.23 (GND), C1.2, C2.2, J1.2, S1.3, S1.4, S2.3, S2.4, S3.3, S3.4, S4.3, S4.4
GND2: D9.K, D10.K, J2.2, Q1.2 (S), R1.2, U4.3 (VINA+), U4.4 (VSS), U4.5 (VINB+)
GND3: J3.2, Q2.2 (S), R4.2, U1.3 (-V), U1.8 (COMMON), U2.3 (-V), U2.8 (COMMON)
unnamed: B1.5 (2), S2.1, S2.2
unnamed: B1.7 (4), S3.1, S3.2
unnamed: B1.8 (*5), S4.1, S4.2
unnamed: B1.22 (RESET), S1.1, S1.2
unnamed: C4.2, D10.A, R3.1, U4.2 (VINA-)
unnamed: C3.1, D9.A, R2.2, U4.6 (VINB-)

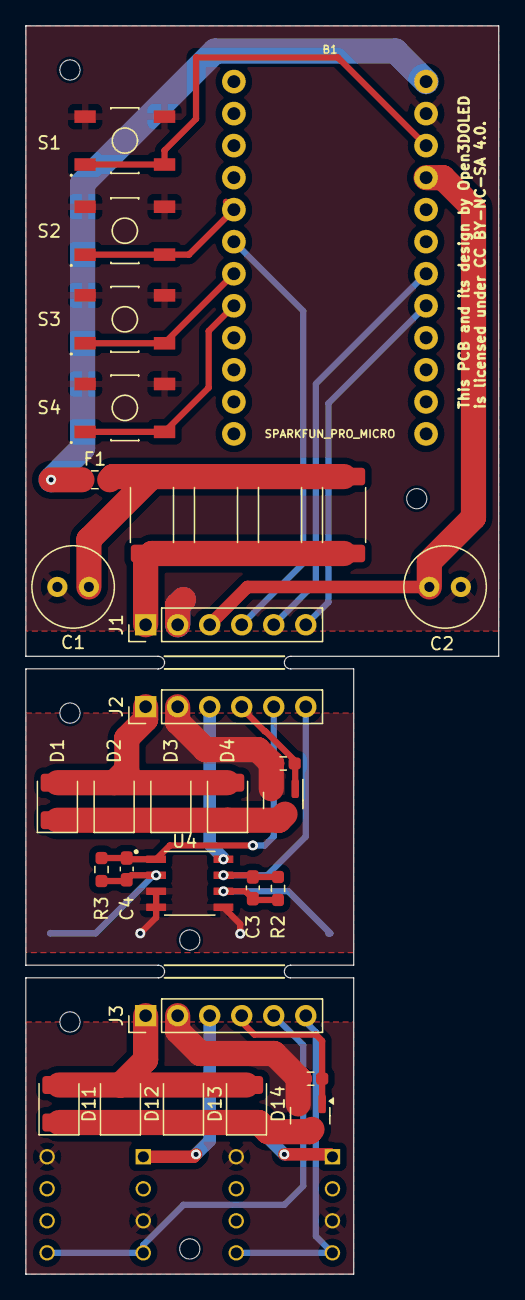
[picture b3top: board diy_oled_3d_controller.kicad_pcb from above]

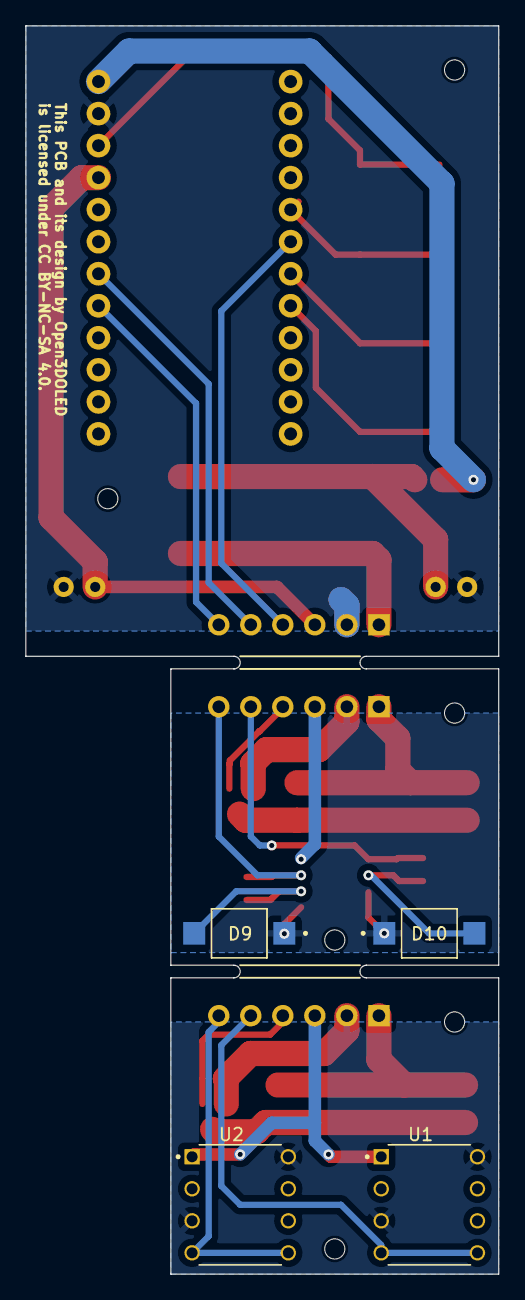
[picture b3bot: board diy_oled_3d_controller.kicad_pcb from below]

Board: 2 copper layers, 37.5 x 99.0 mm, 42 parts (4 on the bottom side), 28 nets.

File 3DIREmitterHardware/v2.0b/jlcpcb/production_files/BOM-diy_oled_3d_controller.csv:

Comment,Designator,Footprint,LCSC
MCP6022-I_SN,U4,SOIC127P599X175-8N,
R,R3,R_0603_1608Metric_Pad0.98x0.95mm_HandSolder,
C,C4,C_0603_1608Metric_Pad1.08x0.95mm_HandSolder,
1000,R1,R_0603_1608Metric_Pad0.98x0.95mm_HandSolder,
TL3342F160QG,S4,SW_TL3342F160QG,
Polyfuse,F1,Fuse_0805_2012Metric_Pad1.15x1.40mm_HandSolder,
LED,D12,LED_1210_3225Metric_Pad1.42x2.65mm_HandSolder,
LED,D1,LED_1210_3225Metric_Pad1.42x2.65mm_HandSolder,
AO3400A,Q1,SOT-23,
C,C3,C_0603_1608Metric_Pad1.08x0.95mm_HandSolder,
LED,D4,LED_1210_3225Metric_Pad1.42x2.65mm_HandSolder,
1.5,R11,R_2512_6332Metric_Pad1.40x3.35mm_HandSolder,
C_Polarized,C1,C_Radial_D6.3mm_H11.0mm_P2.50mm,
Conn_01x06_Pin,J3,PinHeader_1x06_P2.54mm_Vertical,
SPARKFUN_PRO_MICRO,B1,SPARKFUN_PRO_MICRO,
LED,D2,LED_1210_3225Metric_Pad1.42x2.65mm_HandSolder,
TL3342F160QG,S2,SW_TL3342F160QG,
AO3400A,Q2,SOT-23,
Conn_01x06_Pin,J1,PinHeader_1x06_P2.54mm_Vertical,
1.5,R13,R_2512_6332Metric_Pad1.40x3.35mm_HandSolder,
TL3342F160QG,S1,SW_TL3342F160QG,
Conn_01x06_Pin,J2,PinHeader_1x06_P2.54mm_Vertical,
LED,D14,LED_1210_3225Metric_Pad1.42x2.65mm_HandSolder,
LED,D11,LED_1210_3225Metric_Pad1.42x2.65mm_HandSolder,
1.5,R10,R_2512_6332Metric_Pad1.40x3.35mm_HandSolder,
C_Polarized,C2,C_Radial_D6.3mm_H11.0mm_P2.50mm,
1.5,R12,R_2512_6332Metric_Pad1.40x3.35mm_HandSolder,
LED,D13,LED_1210_3225Metric_Pad1.42x2.65mm_HandSolder,
LED,D3,LED_1210_3225Metric_Pad1.42x2.65mm_HandSolder,
1000,R4,R_0603_1608Metric_Pad0.98x0.95mm_HandSolder,
R,R2,R_0603_1608Metric_Pad0.98x0.95mm_HandSolder,
TL3342F160QG,S3,SW_TL3342F160QG,
OPT101P,U2,DIP762W46P254L952H419Q8,
VBPW34S,D9,XDCR_VBPW34S,
VBPW34S,D10,XDCR_VBPW34S,
OPT101P,U1,DIP762W46P254L952H419Q8,

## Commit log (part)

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2024-02-09 added test videos and missing pip requirement
2024-02-09 still trying to fix issue with pyinstaller
2024-02-10 added support to auto select correct serial port when possible
2024-02-10 fix toolbar fullscreen tooltip
2024-02-10 updated readme with lots of details
2024-02-11 added display settings and new calibration options to move whitebox position dynamically during calibration
2024-02-11 fix windows pyinstaller issue
2024-02-11 added license text to PCB model
2024-02-13 fixed fillzone in hardware pcb design wasn't connected to 5V_AFTER_FUSE
2024-03-07 added debug keys for simulating dropped frames
2024-03-07 removed output stats from default profiles as I think it may have increased likelihood of duplicate frames from pc
2024-03-07 fix calibration mode and skip page test keys
2024-03-07 updated tdg-br100 settings
2024-03-15 removed seperate process logic as it wasn't more performant on any platform as far as I could determine and complicated plugin code base
2024-03-16 changed to slower but more accurate seeking to see if it's fast enough for most users as people were having accuracy issues when seeking for short durations
2024-03-18 more fixes and adding support for block_n_subsequent_duplicates (still not implemented just yet)
2024-03-21 improvements for windows pyinstaller version as well as more license details
2024-03-25 tweaks to firmware to get better support for pwm lcd displays
2024-03-27 minor bug fixes and added code to show video time as overlay mouse move also fullscreen on playback is default now
2024-03-30 increase timeout as first time video playback can sometimes take a while to cache all the plugin dlls
2024-03-31 updated readme added v12 firmware to repo updated defaults fixed calibration video added pacman msys2 package database files for last working build version
2024-03-31 testing new environment variable for windows
2024-04-01 updated readme and removed unnecessary code
2024-04-03 updated mount scad files for lg c1 55 inch
2024-04-03 disabled filtering of signal but kept power fix
2024-04-05 changed to playbin3 as it will support more features and has claimed performance improvements
2024-04-06 custom settings file for sony fix to gstpageflipglsink updated gitignore
2024-04-06 renamed enable_smart_duplicate_frame_handling to duplicate_realtime_reporting in 3d player
2024-04-06 added duplicate frame count to OSD in calibration mode
2024-04-08 add open video options for "generate dot graph file" and "decoder preference"
2024-04-08 improvement to handling of displaying the osd settings and duplicates
2024-04-08 added audio format filter and fixed issues where the player would hang when gstreamer couldn't build a valid pipeline
2024-04-08 moved command line parser above all the gst imports so that if you are running --help it wont take as long before exiting
2024-04-08 trying again with the arg parser to get it parse before loading libraries
2024-04-10 added text cache for subtitle strings fixed some other bugs
2024-04-15 refactored to multiple files
2024-04-15 fixes to WS_POPUP logic after windows testing
2024-04-16 redirect stderr to None too for pygame import
2024-04-20 added sensor logging hotkey to calibration mode
2024-04-21 removed lcd specific timer based duplicate frame detection because it was too complicated and I don't think anyone will ever use it, it seems very fast same frame recover on duplicates isn't that imp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
2024-04-22 added some code and examples to allow for calibration of viewsonic xg2431 with purexp bfi custom settings via dccutil in linux (this calibration mode for xg2431 only works in linux)
2024-04-22 fixing some subtitle related issues
2024-04-22 added subtitle and video clear buttons and thanks dialog
2024-04-24 first attempt and windows menu on top hack
2024-04-24 changes to firmware 14
2024-04-24 missing comma
2024-04-24 added disable-3d-on-mouse-move-under-windows option to display settings
2024-04-25 updated readme with notes about windows 10/11 high dpi scaling disable setting for just 3d_player.exe
2024-04-28 wip first commit of switching trigger boxes to colored opengl vertices instead of texture sort of working lets get a snapshot of it before I break it while trying to fix it....
2024-04-28 gadient tweaks
2024-04-29 added git ignore for 3mf files and cleaned up some measurements
2024-05-01 some minor fixes to pcb schamtic values for opamp passives
2024-05-01 added sample stl for lg c1 55
2024-05-01 change default file selection logic to use user defined default format if file name has no relevant data
2024-05-01 added blackbox border setting
2024-05-06 added default v2 display settings profile
2024-05-12 3d player label fix
2024-05-13 fixed more readme alignment issues
2024-05-13 added another note to the readme.
2024-05-14 fixed readme issue
2024-05-14 re-added v1 pcb for historical reasons to master
2024-05-15 added a v2.2 openscad with screw holes and window size changed...
2024-05-17 fixed handling of 2 signal combined open close protocols
2024-05-19 added an additiona display config and refresh rate for xg2431
2024-05-21 added avs script export from display settings window
2024-05-22 removed references to opt101 from settings and 3d player (support old json files with opt101 for backwards compatability)
2024-05-22 added threshold low to emitter firmware and renamed above_threshold to triggered to reflect the fact it now covers multiple conditions
2024-05-22 removed unnecessary variable
2024-05-22 bug fix for avs script generator
2024-05-24 fixed formatting on readme
2024-05-28 updated build script for cad design 0202 also added window area for acrylic insert once I find one that doesn't block too much ir
2024-05-29 we don't want status leds turned on in default build and added v17 firmware
2024-05-29 updated table again
2024-05-30 made another change to firmware v17b to deal dropped frames on pwm displays when timing mode was active, we need to increment the frame counter still or our average frametime becomes inaccurate.
2024-05-31 reworked all the logic for pwm backlit displays lets get them sinking properly instead of relying on using to high values for block signal detection delay, from now on using the pwm specific settings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
2024-06-03 updated algorithm now works perfectly on OLED without BFI enabled and probably on LCD's without BFI too!!!
2024-07-04 added lg cx dimensions to scad updated custom glasses ir settings profile to include frametime and pwm for c1 oled
2024-07-27 added some new tv bezel sizes
2024-07-31 swallow the memory view error for now
2024-07-31 another error type
2024-07-31 more tweaks to support hdmiin
2024-08-05 fixes to calibration test procedure
2024-08-20 added potplayer avs scripts for my two dislays
2024-08-22 added cuda to list of caps for gstpageflipglsink
2024-08-22 moved target framerate to bottom to avoid anyone setting it without knowing the consequences
2024-09-09 trying to get readme indents to appear properly
2024-09-09 added a video showing disabling ALLM using CRU.
2024-09-18 added polarization note regarding pc monitors +/- 45 polarization
2024-09-27 readme change and added Sony 90CL SCAD parameters
2024-10-07 updated prices to reflect low inventory for high number of cracked frames when trying to exchange batteries.
2024-10-07 add hisense 100U7K dimensions
2025-01-28 Update README.md
    Added more specific notes concerning gaming
2025-02-05 added support for ir drive mode pc serial to use with wibble wobble
2025-02-05 wip update to averaging algorithm
2025-02-06 more changes to use averaging
2025-02-07 removed all unused parameters from ir_signal_process_trigger
2025-02-07 moved over first copy of averaging logic
2025-02-07 removed ir averaging mode code from opt detection module now it just lives in the shared ir_signals.cpp file
2025-02-07 generic fixes for when we detect an error
2025-02-08 fixes for resync on dropped frames
2025-02-11 updated 20a firmware
2025-02-11 tuned parameter on balancng so that it can rebalance left/right phase drift over larger range as 500us was insufficient
2025-02-11 fixed a bug where it was not saving ir_average_timing_mode properly to settings files for re-use
2025-02-12 updated image with fixes
2025-02-16 sample avs script that includes basic parallax adjustment for full side by side and half side by side
2025-05-02 initial dlplink sensor commit
2025-05-02 no auto function for now
2025-05-04 got it working much better using lighter interrupt routine and not micros time based detection.
2025-05-09 better handling of boundry conditions and xgimi aura output as well as some debug lines
2025-05-09 various tweaks and fixes for dlp sensor mode
2025-05-09 some sample dlplink sensor profiles
2025-05-09 cleanup and added eye swap button support on switch4 d5
2025-05-10 added a sanity check to turn things off when there are no significant oscilliations in light levels to prevent us miss detecting micro fluctuations as dlplink pulses also fixed flipped eye button tog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
2025-05-10 parameterized the various permutations of the relay case design
2025-05-11 added sample stl for relay case with minidin3 input and eye swap button
2025-05-31 dlplink trigger mode using jx30 module fixes (needs proper DC isolation using large 1000uF or 4700uF capacitor and DC isolator otherwise Vcc ripple interferes with dlplink sync lock based on analog o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
2025-06-01 more changes to dlp link mode (need to fix averaging mode some more still)
2025-06-02 tuned settings for xgimi aura
2025-07-12 added split base mount option to openscad model for users who want to mount the sensor and main unit on tv's with varying thickness (doesn't support covers for now).
2025-07-13 added emitter config for lg c1 without 120hz bfi available
2025-07-19 added test version of serial sync from 3d player
2025-07-29 add additional settings for xg2431
2025-07-29 cleaned up software sync mode to use signal instead of polling
2025-08-07 Added note about issue with AMD drivers switching to 60 hz and a temporary work around
2025-08-13 Update README.md
    People are having trouble finding the releases page on github
2025-08-25 updated the default ghosting test video to make it much longer fixed out dated settings updated invalid resolution guidance for sony tv in menus.
2025-08-27 Added experimental software sync background mode for use with PotPlayer without needing to mount the unit on the TV. This is experimental as it isn't clear if PotPlayer frame sequential will maintain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
2025-08-27 Added contact and discord details to readme
2025-08-28 added get pixel logic to determine which eye toshow
2025-09-01 WIP v1 with getPixel and line profiler
2025-09-01 simple test script that uses opengl window instead of pygame for sync detection
2025-09-02 need alternative to pygame for vsync as it is too cpu intensive i think
2025-09-02 background sync mode get pixel mode
2025-09-02 first commit of reshade plugin
2025-09-02 partial working
2025-09-02 wip still some issues with the create resource having invalid parameters
2025-09-03 more changes to get it working with shader copy-back technique
2025-09-03 reverted to old version and it was working but I broke something I need to undo stuff and then do a git compare
2025-09-03 another backup file
2025-09-03 added all files related to getting reshade 6.4.1 working in PotPlayer with trigger boxes and serial syncing
2025-09-03 add 3DPlayer/debug folder back to gitignore
2025-09-03 added link for reshade injector
2025-09-03 added note to ReShade readme about using newest firmware with improve PID averaging
2025-09-05 updated some readme with user feedback
2025-09-25 added glfw requirement that was missing
2025-10-28 added note about xg2431 3d ghosted alternative image frames to the xg2431 setup txt. Now we know why this happens it makes me feel a bit better :)
2026-01-06 xg2431 frame doubling tests
2026-01-11 switched to 115200 not sure why we were using 118200 I believe it should be able to recover for update but I will tell people to update their firmware before updating to this version if I notice prob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
2026-01-11 some random frame doubling settings profiles
2026-01-11 fix for mode switch reseting opt parameters
2026-02-28 updated mpcvideorenderer and documentation
2026-03-24 Track VLCModule as a main-branch submodule
2026-05-02 sample code (totally untested) illustrating how to handle variable frame repition counts in cyclical frame sequence for blur reduction detection mode.
2026-05-15 Guard optical emitter timing settings

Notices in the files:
README.md:
Licenses:
Please refer to LICENSE files and license folders for references to open source licenses. If you find any missing licenses please open a support ticket.
Open3DOLED is licensed under CC BY-NC-SA 4.0
